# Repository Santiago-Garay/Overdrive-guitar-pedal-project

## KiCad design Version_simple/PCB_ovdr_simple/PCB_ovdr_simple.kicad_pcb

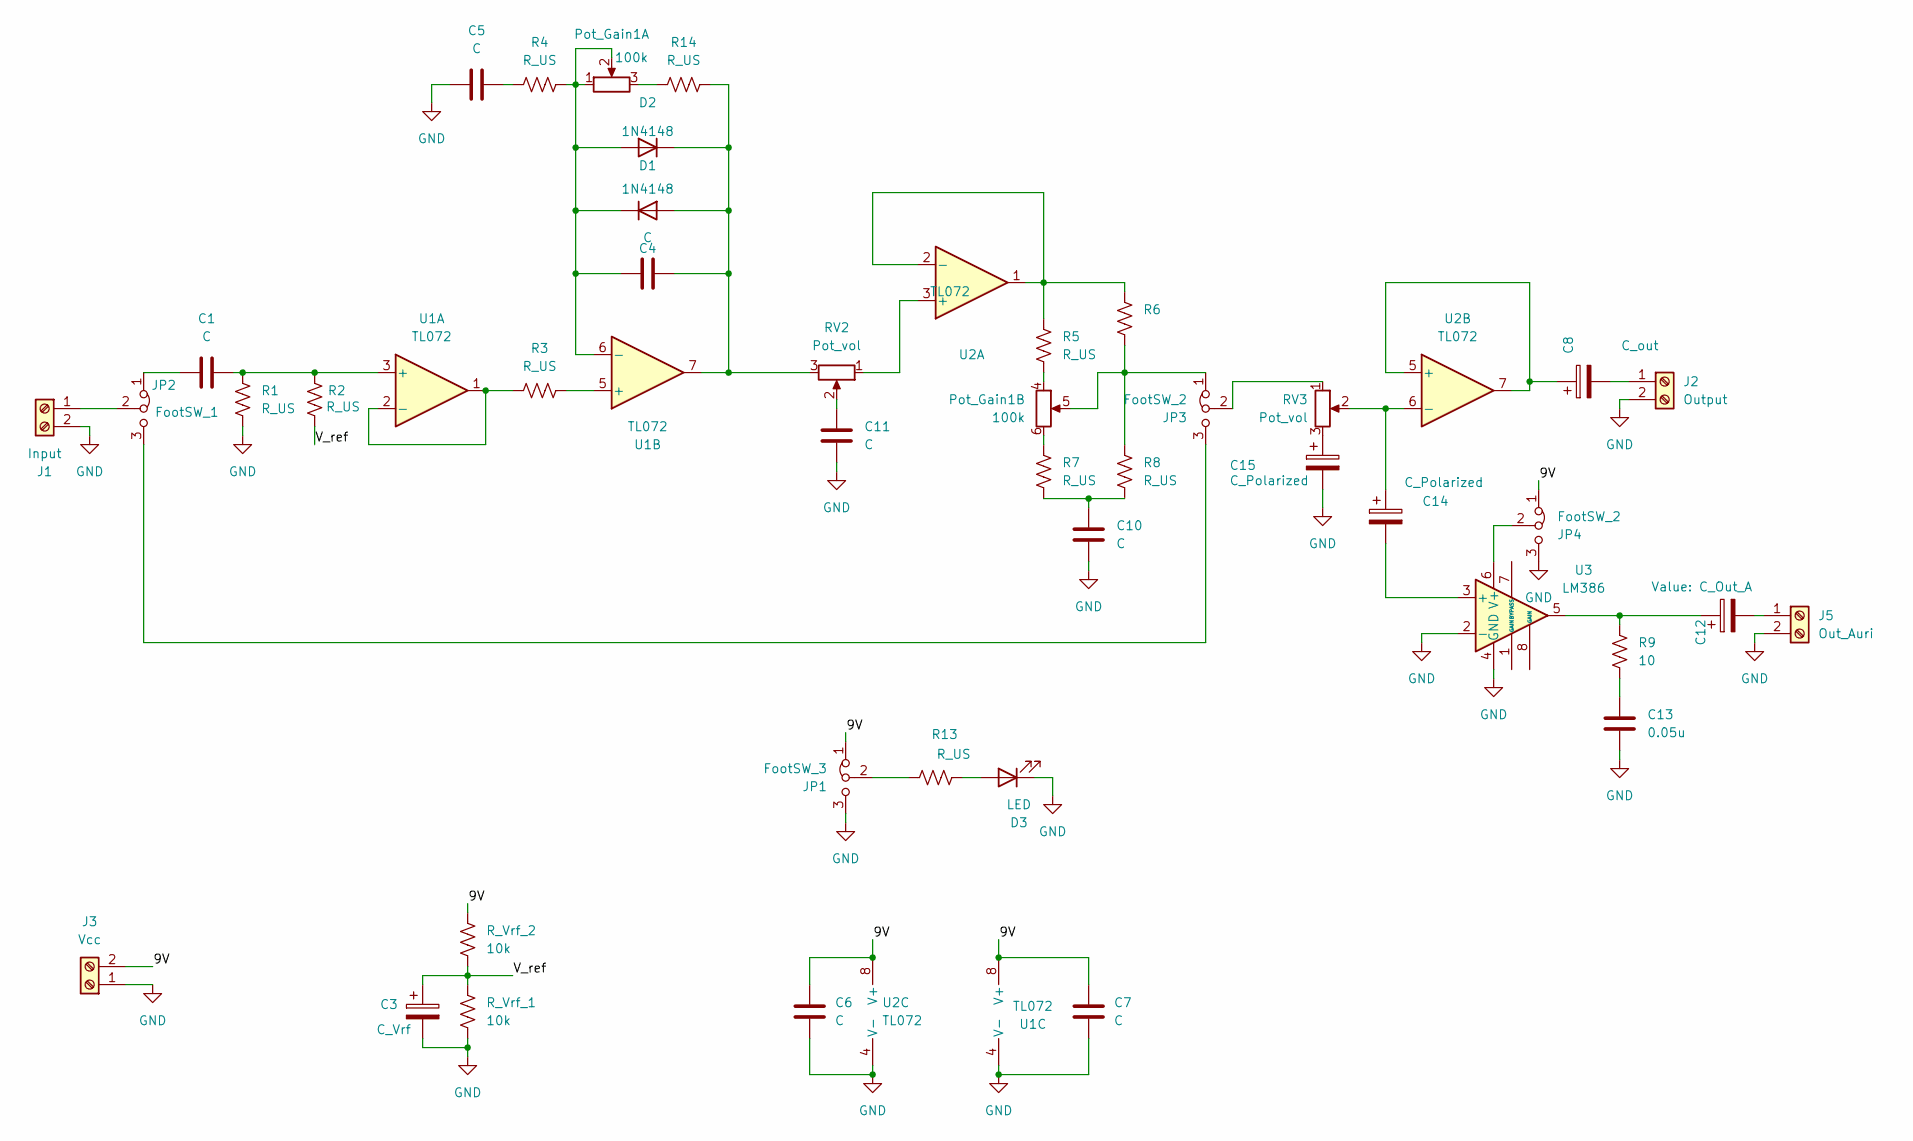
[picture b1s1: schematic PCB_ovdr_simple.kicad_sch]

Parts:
C1, C4, C5, C6, C7, C10, C11: C; C_Disc_D7.0mm_W2.5mm_P5.00mm
C3: C_Vrf; C_Radial_D10.0mm_H16.0mm_P5.00mm
C8: C_out; C_Radial_D10.0mm_H16.0mm_P5.00mm
C12: C_Out_A; C_Radial_D10.0mm_H16.0mm_P5.00mm
C13: 0.05u; C_Disc_D7.0mm_W2.5mm_P5.00mm
C14: C_Polarized; C_Radial_D10.0mm_H16.0mm_P5.00mm
C15: C_Polarized; C_Radial_D6.3mm_H5.0mm_P2.50mm
D1, D2: 1N4148; D_DO-35_SOD27_P7.62mm_Horizontal
D3: LED; PinSocket_1x02_P2.54mm_Vertical
J1: Input; TerminalBlock_MaiXu_MX126-5.0-02P_1x02_P5.00mm
J2: Output; TerminalBlock_MaiXu_MX126-5.0-02P_1x02_P5.00mm
J3: Vcc; TerminalBlock_MaiXu_MX126-5.0-02P_1x02_P5.00mm
J5: Out_Auri; TerminalBlock_MaiXu_MX126-5.0-02P_1x02_P5.00mm
JP1: FootSW_3; PinSocket_1x03_P2.54mm_Vertical
JP2: FootSW_1; PinSocket_1x03_P2.54mm_Vertical
JP3, JP4: FootSW_2; PinSocket_1x03_P2.54mm_Vertical
Pot_Gain1: 100k; PinSocket_2x03_P2.54mm_Vertical
R1, R2, R3, R4, R5, R6, R7, R8, R13, R14: R_US; R_Axial_DIN0207_L6.3mm_D2.5mm_P10.16mm_Horizontal
R9: 10; R_Axial_DIN0207_L6.3mm_D2.5mm_P10.16mm_Horizontal
RV2, RV3: Pot_vol; PinSocket_1x03_P2.54mm_Vertical
R_Vrf_1, R_Vrf_2: 10k; R_Axial_DIN0207_L6.3mm_D2.5mm_P10.16mm_Horizontal
U1, U2: TL072; DIP-8_W7.62mm_LongPads
U3: LM386; DIP-8_W7.62mm_LongPads

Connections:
/9V: C6.2, C7.2, J3.2, JP1.1 (A), JP4.1 (A), R_Vrf_2.1, U1.8 (V+), U2.8 (V+)
/V_ref: C3.1, R2.2, R_Vrf_1.1, R_Vrf_2.2
GND: C3.2, C5.1, C6.1, C7.1, C10.1, C11.1, C13.1, C15.2, D3.1 (K), J1.2, J2.2, J3.1, J5.2, JP1.3 (B), JP4.3 (B), R1.2, R_Vrf_1.2, U1.4 (V-), U2.4 (V-), U3.2 (-), U3.4 (GND)
unnamed: C5.2, R4.1
unnamed: C10.2, R7.1, R8.1
unnamed: C11.2, RV2.2
unnamed: C12.1, R9.2, U3.5
unnamed: C13.2, R9.1
unnamed: C15.1, RV3.3
unnamed: C4.2, D1.2 (A), D2.1 (K), R14.2, RV2.3, U1.7
unnamed: C4.1, D1.1 (K), D2.2 (A), Pot_Gain1.1, Pot_Gain1.2, R4.2, U1.6 (-)
unnamed: D3.2 (A), R13.2
unnamed: J1.1, JP2.2 (C)
unnamed: C8.2, J2.1
unnamed: C12.2, J5.1
unnamed: JP1.2 (C), R13.1
unnamed: C1.1, JP2.1 (A)
unnamed: JP2.3 (B), JP3.3 (B)
unnamed: JP3.1 (A), Pot_Gain1.5, R6.1, R8.2
unnamed: JP3.2 (C), RV3.1
unnamed: JP4.2 (C), U3.6 (V+)
unnamed: Pot_Gain1.3, R14.1
unnamed: Pot_Gain1.4, R5.1
unnamed: Pot_Gain1.6, R7.2
unnamed: C1.2, R1.1, R2.1, U1.3 (+)
unnamed: R3.1, U1.1, U1.2 (-)
unnamed: R3.2, U1.5 (+)
unnamed: RV2.1, U2.3 (+)
unnamed: R5.2, R6.2, U2.1, U2.2 (-)
unnamed: C8.1, U2.5 (+), U2.7
unnamed: C14.1, RV3.2, U2.6 (-)
unnamed: C14.2, U3.3 (+)

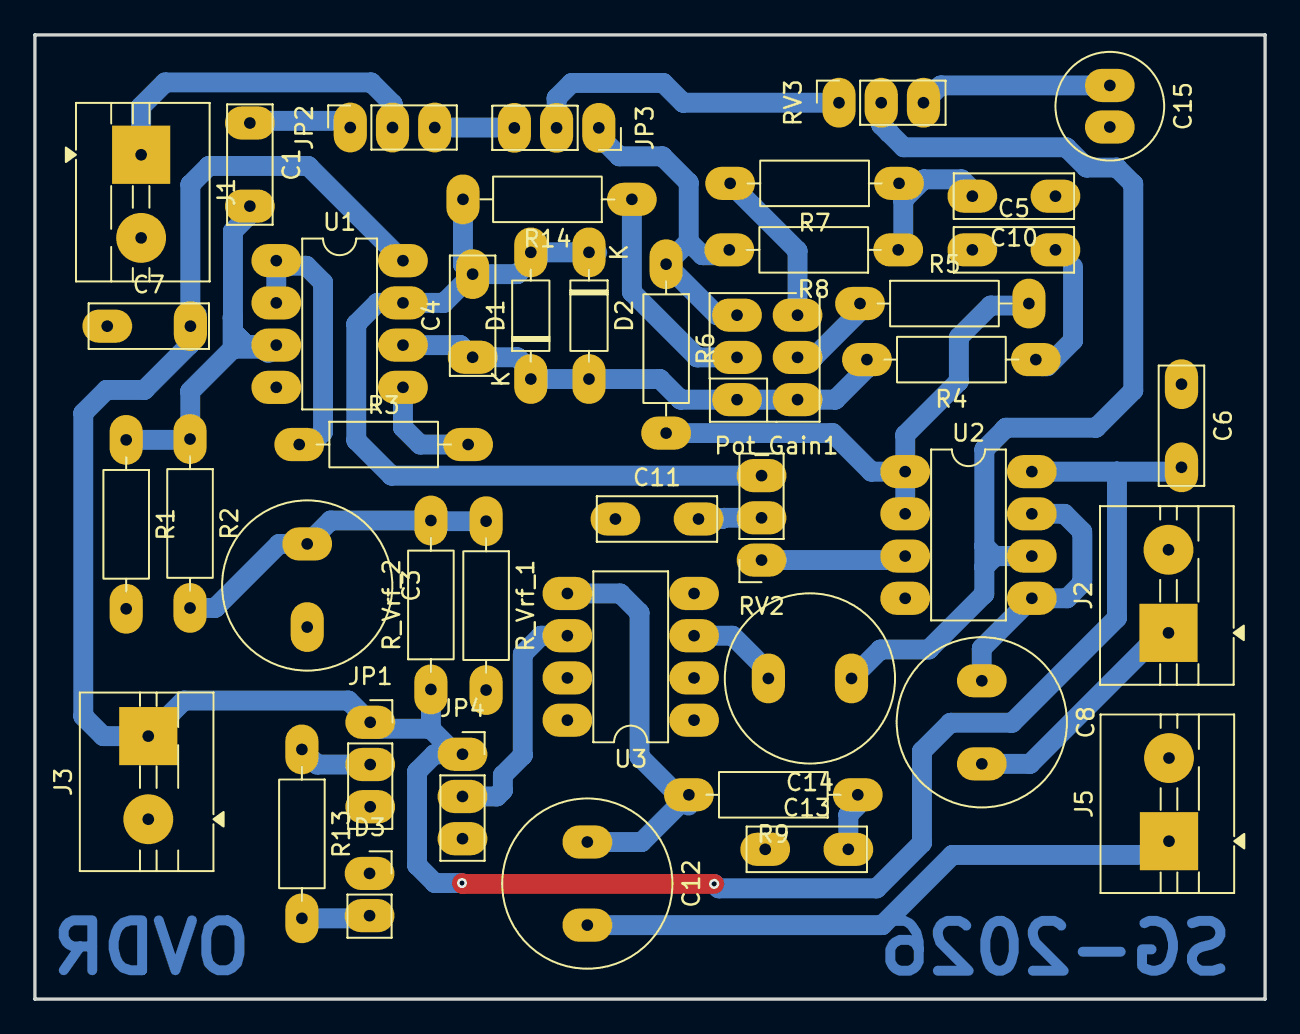
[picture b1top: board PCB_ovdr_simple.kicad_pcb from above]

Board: 2 copper layers, 74.0 x 58.0 mm, 43 parts (0 on the bottom side), 32 nets.

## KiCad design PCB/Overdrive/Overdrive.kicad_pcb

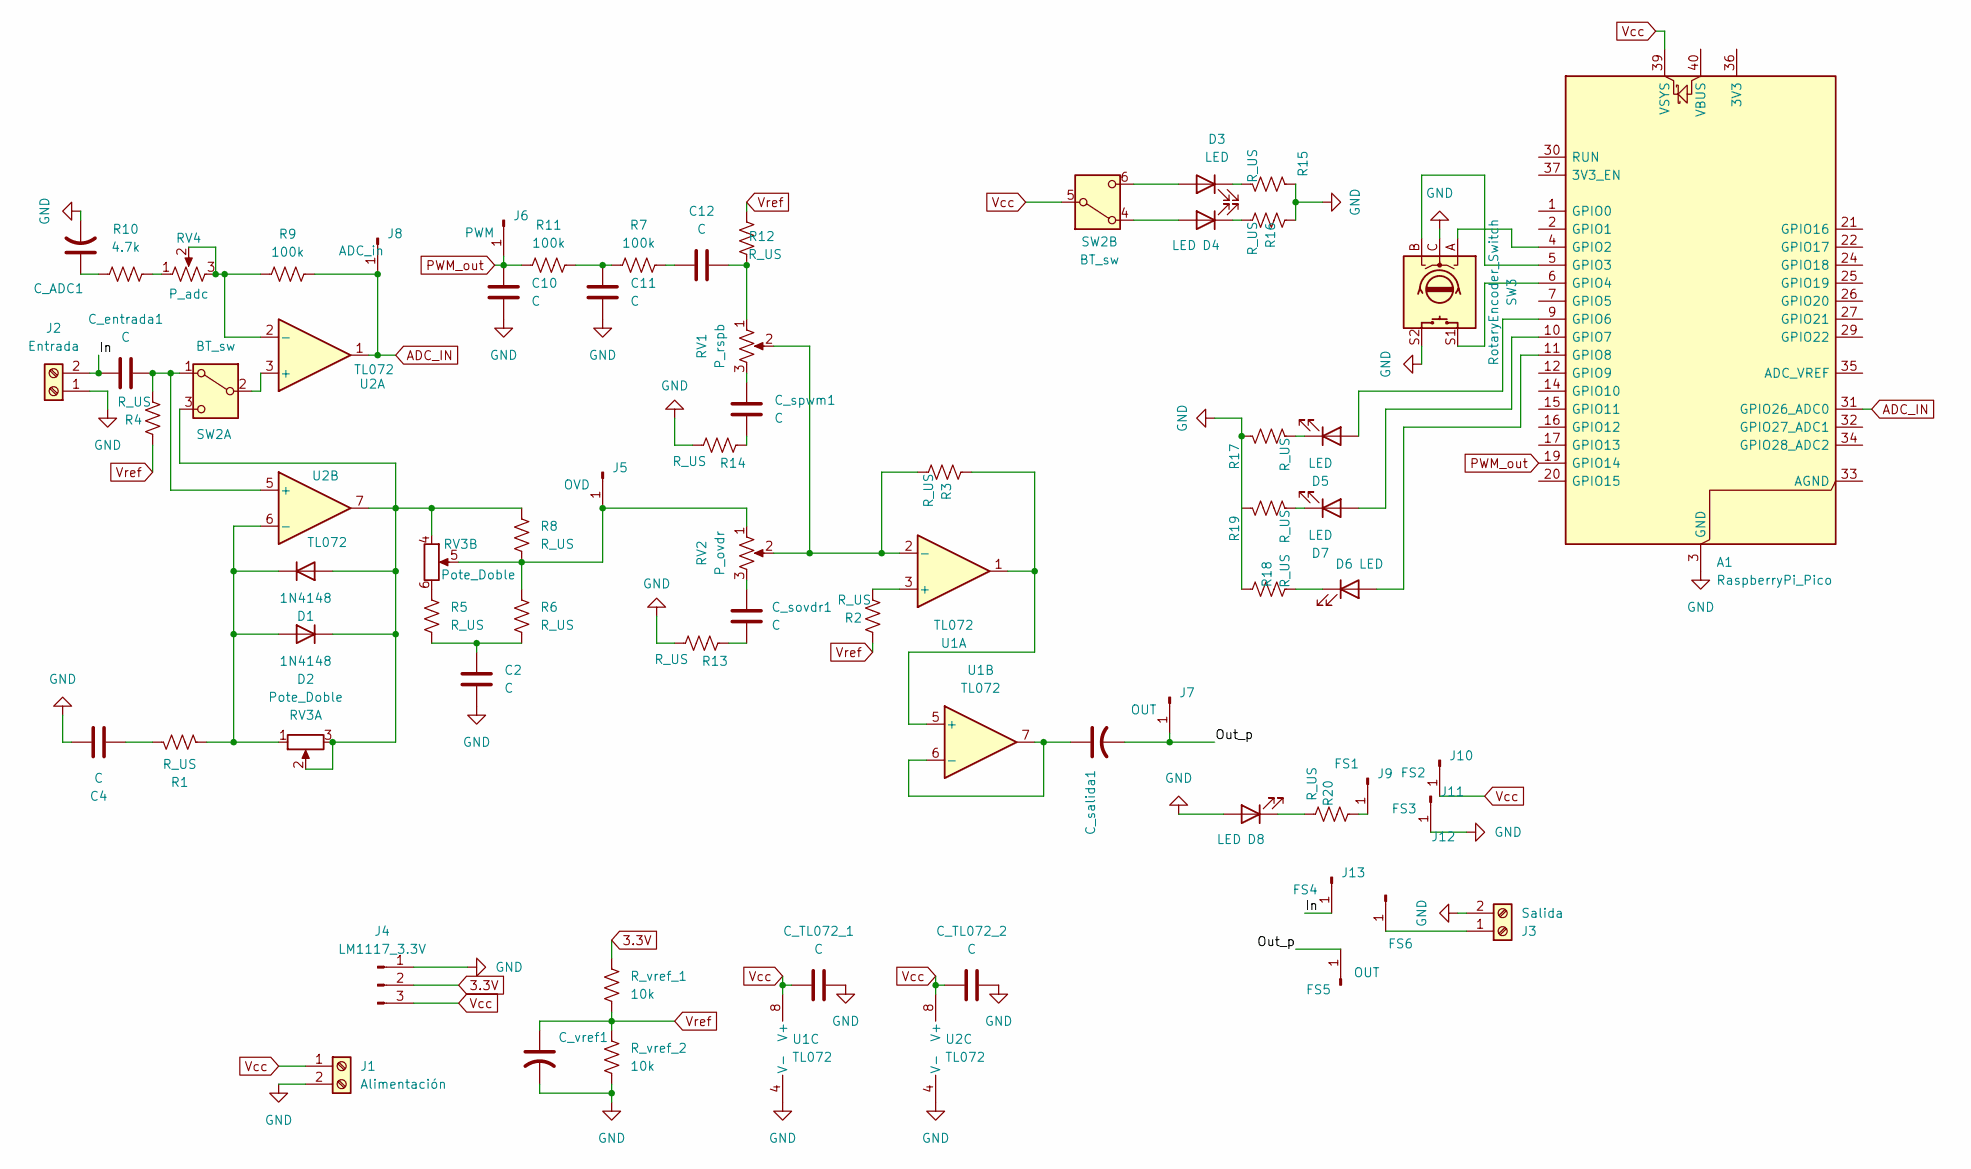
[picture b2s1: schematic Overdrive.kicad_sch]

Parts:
A1: RaspberryPi_Pico; RaspberryPi_Pico_Common_Unspecified
C2, C4, C10, C11, C12: C; CP_Radial_Tantal_D5.5mm_P5.00mm
C_ADC1: CP_Radial_D10.0mm_P5.00mm
C_TL072_1, C_TL072_2: C; CP_Radial_Tantal_D5.5mm_P5.00mm
C_entrada1: C; CP_Radial_Tantal_D5.5mm_P5.00mm
C_salida1: CP_Radial_D10.0mm_P5.00mm
C_sovdr1: C; CP_Radial_Tantal_D5.5mm_P5.00mm
C_spwm1: C; CP_Radial_Tantal_D5.5mm_P5.00mm
C_vref1: CP_Radial_D10.0mm_P5.00mm
D1, D2: 1N4148; D_DO-35_SOD27_P7.62mm_Horizontal
D3, D4, D5, D6, D7, D8: LED; LED_D5.0mm_FlatTop
FS5: OUT; PinHeader_1x01_P2.54mm_Vertical
J1: Alimentación; TerminalBlock_MaiXu_MX126-5.0-02P_1x02_P5.00mm
J2: Entrada; TerminalBlock_MaiXu_MX126-5.0-02P_1x02_P5.00mm
J3: Salida; TerminalBlock_MaiXu_MX126-5.0-02P_1x02_P5.00mm
J4: LM1117_3.3V; PinHeader_1x03_P2.54mm_Vertical
J5: OVD; PinHeader_1x01_P2.54mm_Vertical
J6: PWM; PinHeader_1x01_P2.54mm_Vertical
J7: OUT; PinHeader_1x01_P2.54mm_Vertical
J8: ADC_in; PinHeader_1x01_P2.54mm_Vertical
J9: FS1; PinHeader_1x01_P2.54mm_Vertical
J10: FS2; PinHeader_1x01_P2.54mm_Vertical
J11: FS3; PinHeader_1x01_P2.54mm_Vertical
J12: FS6; PinHeader_1x01_P2.54mm_Vertical
J13: FS4; PinHeader_1x01_P2.54mm_Vertical
R1, R2, R3, R4, R5, R6, R8, R12, R13, R14, R15, R16, R17, R18, R19, R20: R_US; R_Axial_DIN0207_L6.3mm_D2.5mm_P10.16mm_Horizontal
R7, R9, R11: 100k; R_Axial_DIN0207_L6.3mm_D2.5mm_P10.16mm_Horizontal
R10: 4.7k; R_Axial_DIN0207_L6.3mm_D2.5mm_P10.16mm_Horizontal
RV1: P_rspb; PinHeader_1x03_P2.54mm_Vertical
RV2: P_ovdr; PinHeader_1x03_P2.54mm_Vertical
RV3: Pote_Doble; PinSocket_2x03_P2.54mm_Vertical
RV4: P_adc; PinHeader_1x03_P2.54mm_Vertical
R_vref_1, R_vref_2: 10k; R_Axial_DIN0207_L6.3mm_D2.5mm_P10.16mm_Horizontal
SW2: BT_sw; PinSocket_2x03_P2.54mm_Vertical
SW3: RotaryEncoder_Switch; PinSocket_1x05_P2.54mm_Vertical
U1, U2: TL072; DIP-8_W7.62mm_Socket

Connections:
3.3V: J4.2, R_vref_1.1
/In: C_entrada1.1, J2.2, J13.1 (Pin_1_1)
/Out_p: C_salida1.2, FS5.1 (Pin_1_1), J7.1 (Pin_1_1)
ADC_IN: A1.31 (GPIO26_ADC0), J8.1 (Pin_1_1), R9.2, U2.1
GND: A1.3 (GND), A1.8 (GND), A1.13 (GND), A1.18 (GND), A1.23 (GND), A1.28 (GND), A1.38 (GND), C2.1, C4.1, C10.1, C11.1, C_ADC1.2, C_TL072_1.1, C_TL072_2.1, C_vref1.2, D8.2 (A), J1.2, J2.1, J3.2, J4.1, J11.1 (Pin_1_1), R13.1, R14.1, R15.2, R16.2, R17.2, R18.2, R_vref_2.2, SW3.C, SW3.S2, U1.4 (V-), U2.4 (V-)
unnamed: A1.4 (GPIO2), SW3.A
unnamed: A1.5 (GPIO3), SW3.B
unnamed: A1.6 (GPIO4), SW3.S1
unnamed: A1.9 (GPIO6), D5.2 (A)
unnamed: A1.10 (GPIO7), D7.2 (A)
unnamed: A1.11 (GPIO8), D6.2 (A)
unnamed: C2.2, R5.2, R6.2
unnamed: C4.2, R1.1
unnamed: C11.2, R7.1, R11.2
unnamed: C12.1, R7.2
unnamed: C12.2, R12.1, RV1.1
unnamed: C_ADC1.1, R10.1
unnamed: C_sovdr1.1, R13.2
unnamed: C_sovdr1.2, RV2.3
unnamed: C_spwm1.1, R14.2
unnamed: C_spwm1.2, RV1.3
unnamed: D1.2 (A), D2.1 (K), R8.1, RV3.2, RV3.3, RV3.4, SW2.3 (C), U2.7
unnamed: D1.1 (K), D2.2 (A), R1.2, RV3.1, U2.6 (-)
unnamed: D3.2 (A), SW2.6 (C)
unnamed: D3.1 (K), R15.1
unnamed: D4.2 (A), SW2.4 (A)
unnamed: D4.1 (K), R16.1
unnamed: D5.1 (K), R17.1
unnamed: D6.1 (K), R18.1
unnamed: D7.1 (K), R19.1
unnamed: D8.1 (K), R20.1
unnamed: J5.1 (Pin_1_1), R6.1, R8.2, RV2.1, RV3.5
unnamed: J9.1 (Pin_1_1), R20.2
unnamed: J3.1, J12.1 (Pin_1_1)
unnamed: R5.1, RV3.6
unnamed: R10.2, RV4.1
unnamed: C_entrada1.2, R4.1, SW2.1 (A), U2.5 (+)
unnamed: SW2.2 (B), U2.3 (+)
unnamed: R2.1, U1.3 (+)
unnamed: R3.1, RV1.2, RV2.2, U1.2 (-)
unnamed: R3.2, U1.1, U1.5 (+)
unnamed: C_salida1.1, U1.6 (-), U1.7
unnamed: R9.1, RV4.2, RV4.3, U2.2 (-)
PWM_out: A1.19 (GPIO14), C10.2, J6.1 (Pin_1_1), R11.1
Vcc: A1.39 (VSYS), C_TL072_1.2, C_TL072_2.2, J1.1, J4.3, J10.1 (Pin_1_1), SW2.5 (B), U1.8 (V+), U2.8 (V+)
Vref: C_vref1.1, R2.2, R4.2, R12.2, R_vref_1.2, R_vref_2.1

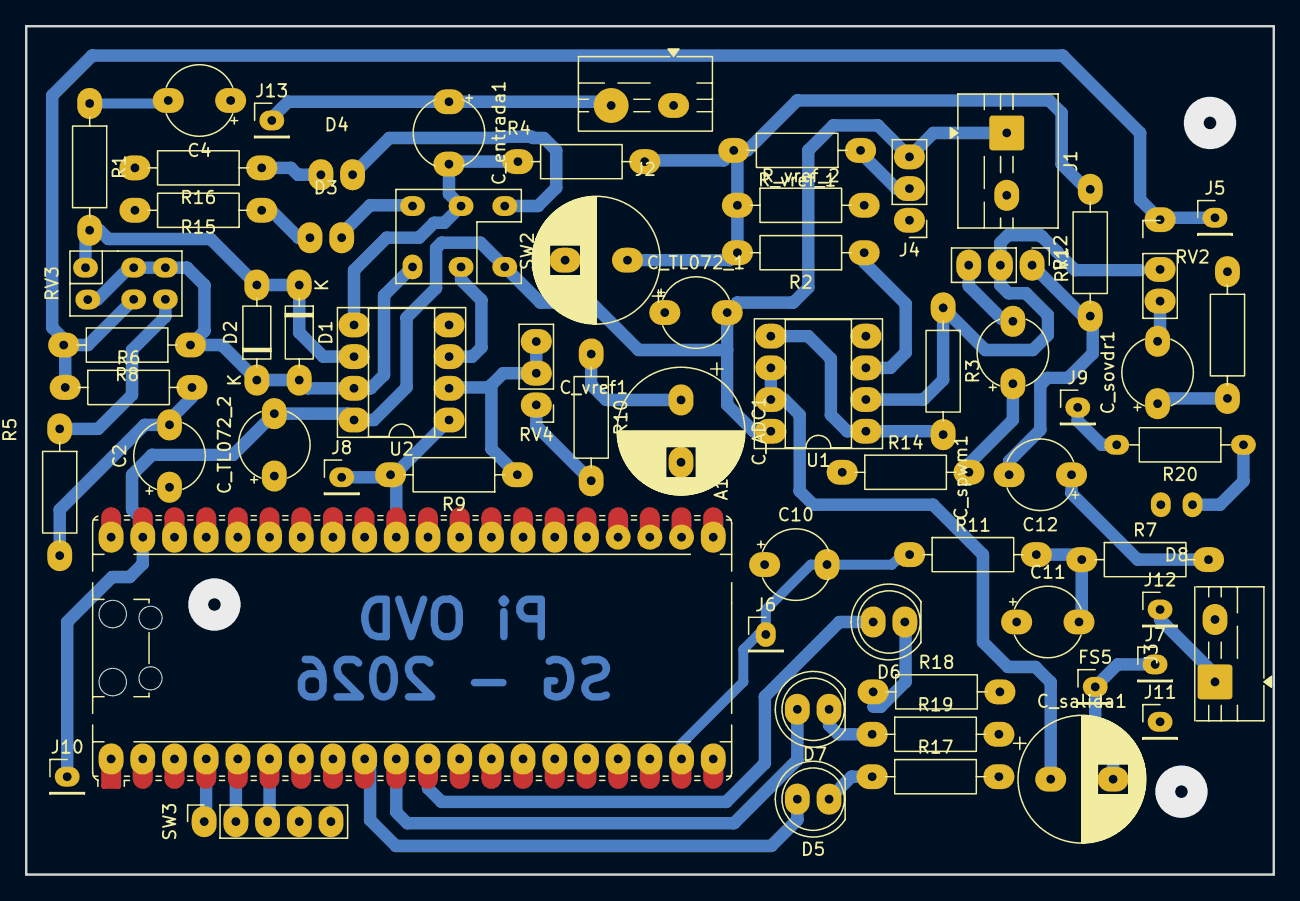
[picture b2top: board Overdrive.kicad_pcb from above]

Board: 2 copper layers, 100.0 x 68.0 mm, 66 parts (0 on the bottom side), 46 nets.

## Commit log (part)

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2026-04-20 Creo la carpeta simulaciones y subo un primer prototipo
2026-04-23 Creo la carpeta pcb con el proyecto armado
